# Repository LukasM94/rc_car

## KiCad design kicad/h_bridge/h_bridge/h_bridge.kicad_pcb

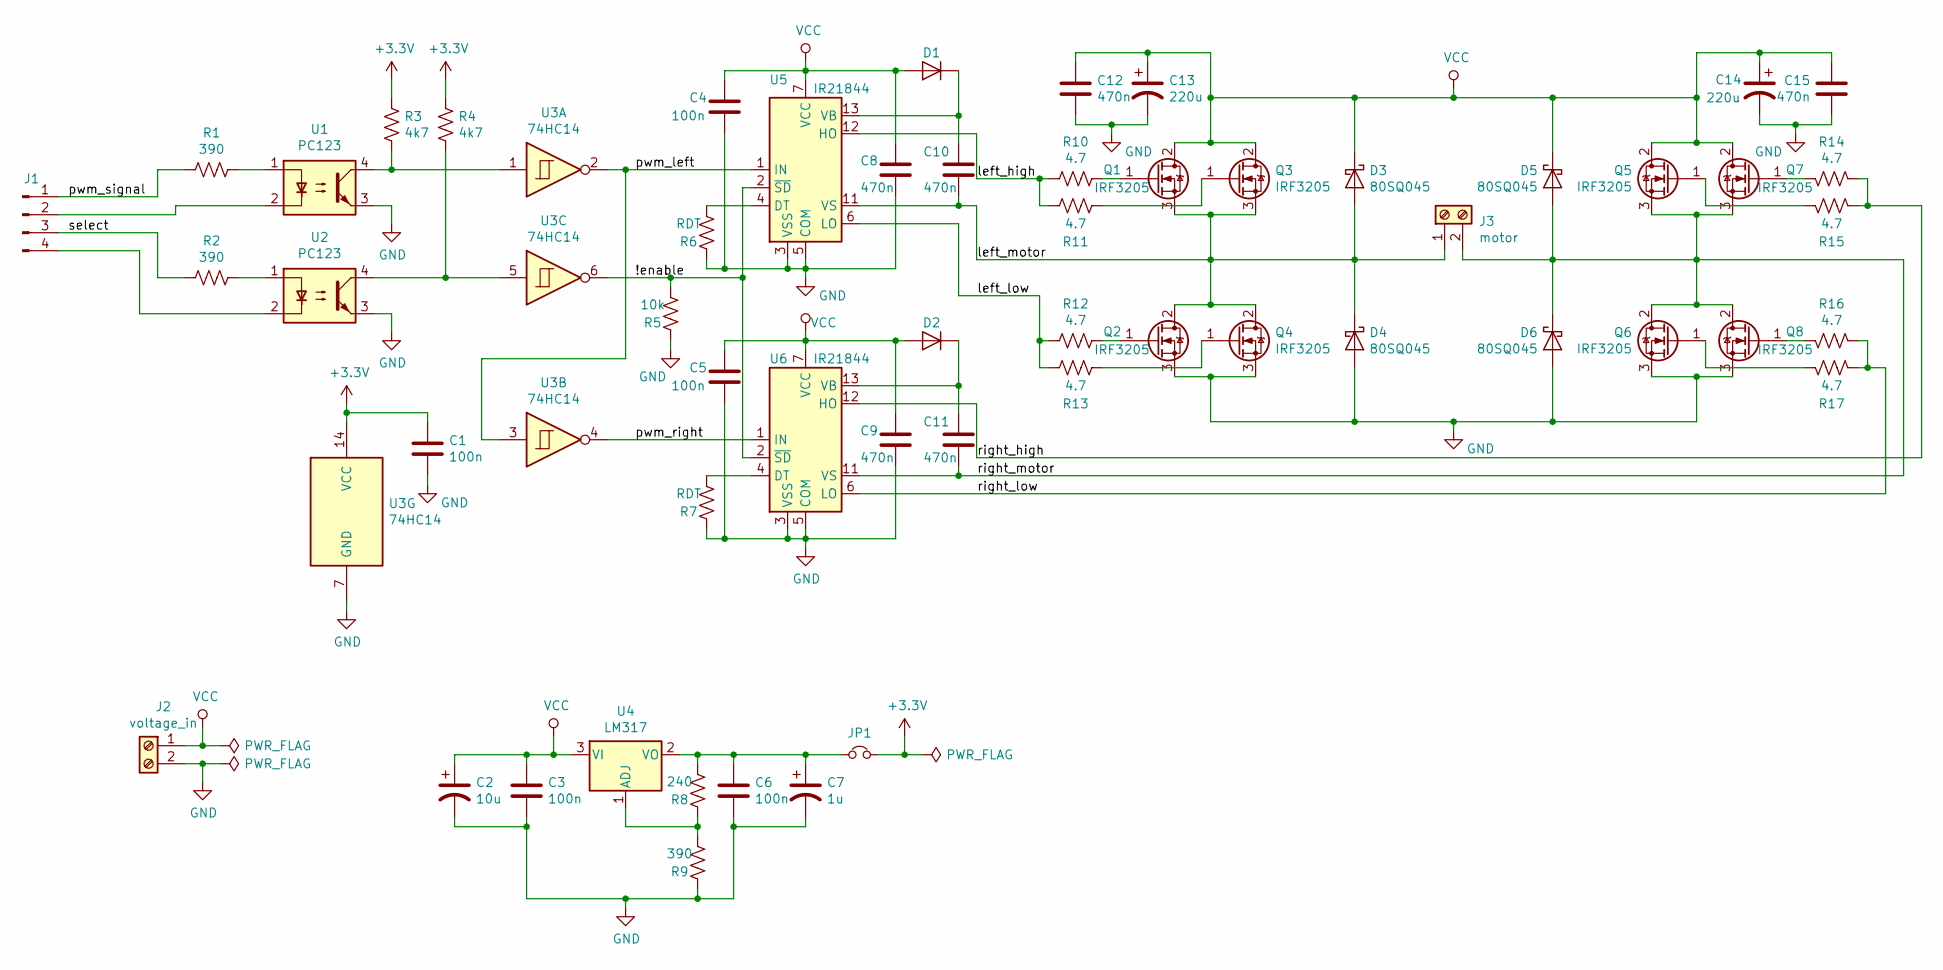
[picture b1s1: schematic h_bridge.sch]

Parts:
C1, C3, C4, C5, C6: 100n; C_0805_2012Metric
C2: 10u; CP_Radial_D5.0mm_P2.50mm
C7: 1u; CP_Radial_D5.0mm_P2.50mm
C8, C9, C10, C11: 470n; C_0805_2012Metric
C12, C15: 470n; C_Rect_L13.0mm_W5.0mm_P10.00mm_FKS3_FKP3_MKS4
C13, C14: 220u; CP_Radial_D10.0mm_P5.00mm
D1, D2: 1N4007; D_DO-41_SOD81_P10.16mm_Horizontal
D3, D4, D5, D6: 80SQ045; D_DO-201AD_P12.70mm_Horizontal
J1: Conn_01x04_Male; PinHeader_1x04_P2.54mm_Vertical
J2: voltage_in; SolderWirePad_1x02_P7.62mm_Drill2.5mm
J3: motor; SolderWirePad_1x02_P7.62mm_Drill2.5mm
JP1: Jumper_NC_Small; PinHeader_1x02_P2.54mm_Vertical
Q1, Q2, Q3, Q4, Q5, Q6, Q7, Q8: IRF3205; TO-220-3_Vertical
R1, R2, R9: 390; R_0805_2012Metric
R3, R4: 4k7; R_0805_2012Metric
R5: 10k; R_0805_2012Metric
R6, R7: RDT; R_0805_2012Metric
R8: 240; R_0805_2012Metric
R10, R11, R12, R13, R14, R15, R16, R17: 4.7; R_0805_2012Metric
U1, U2: PC123; DIP-4_W7.62mm
U3: 74HC14; DIP-14_W7.62mm_LongPads
U4: LM317; TO-220-3_Horizontal_TabDown
U5, U6: IR21844; DIP-14_W7.62mm_LongPads

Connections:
+3V3: C1.1, JP1.2, R3.2, R4.2, U3.14 (VCC)
/!enable: R5.2, U3.6, U5.2 (~SD), U6.2 (~SD)
/left_high: R10.2, R11.2, U5.12 (HO)
/left_low: R12.2, R13.2, U5.6 (LO)
/left_motor: C10.2, D3.2 (A), D4.1 (K), J3.1, Q1.3 (S), Q2.2 (D), Q3.3 (S), Q4.2 (D), U5.11 (VS)
/pwm_left: U3.2, U3.3, U5.1 (IN)
/pwm_right: U3.4, U6.1 (IN)
/pwm_signal: J1.1, R1.2
/right_high: R14.2, R15.2, U6.12 (HO)
/right_low: R16.2, R17.2, U6.6 (LO)
/right_motor: C11.2, D5.2 (A), D6.1 (K), J3.2, Q5.3 (S), Q6.2 (D), Q7.3 (S), Q8.2 (D), U6.11 (VS)
/select: J1.3, R2.2
GND: C1.2, C2.2, C3.2, C4.2, C5.2, C6.2, C7.2, C8.2, C9.2, C12.2, C13.2, C14.2, C15.2, D4.2 (A), D6.2 (A), J2.2, Q2.3 (S), Q4.3 (S), Q6.3 (S), Q8.3 (S), R5.1, R6.1, R7.1, R9.1, U1.3, U2.3, U3.7 (GND), U5.3 (VSS), U5.5 (COM), U6.3 (VSS), U6.5 (COM)
unnamed: C6.1, C7.1, JP1.1, R8.2, U4.2 (VO)
unnamed: C10.1, D1.1 (K), U5.13 (VB)
unnamed: C11.1, D2.1 (K), U6.13 (VB)
unnamed: J1.2, U1.2
unnamed: J1.4, U2.2
unnamed: Q1.1 (G), R10.1
unnamed: Q2.1 (G), R12.1
unnamed: Q3.1 (G), R11.1
unnamed: Q4.1 (G), R13.1
unnamed: Q5.1 (G), R15.1
unnamed: Q6.1 (G), R17.1
unnamed: Q7.1 (G), R14.1
unnamed: Q8.1 (G), R16.1
unnamed: R1.1, U1.1
unnamed: R2.1, U2.1
unnamed: R3.1, U1.4, U3.1
unnamed: R4.1, U2.4, U3.5
unnamed: R6.2, U5.4 (DT)
unnamed: R7.2, U6.4 (DT)
unnamed: R8.1, R9.2, U4.1 (ADJ)
VCC: C2.1, C3.1, C4.1, C5.1, C8.1, C9.1, C12.1, C13.1, C14.1, C15.1, D1.2 (A), D2.2 (A), D3.1 (K), D5.1 (K), J2.1, Q1.2 (D), Q3.2 (D), Q5.2 (D), Q7.2 (D), U4.3 (VI), U5.7 (VCC), U6.7 (VCC)

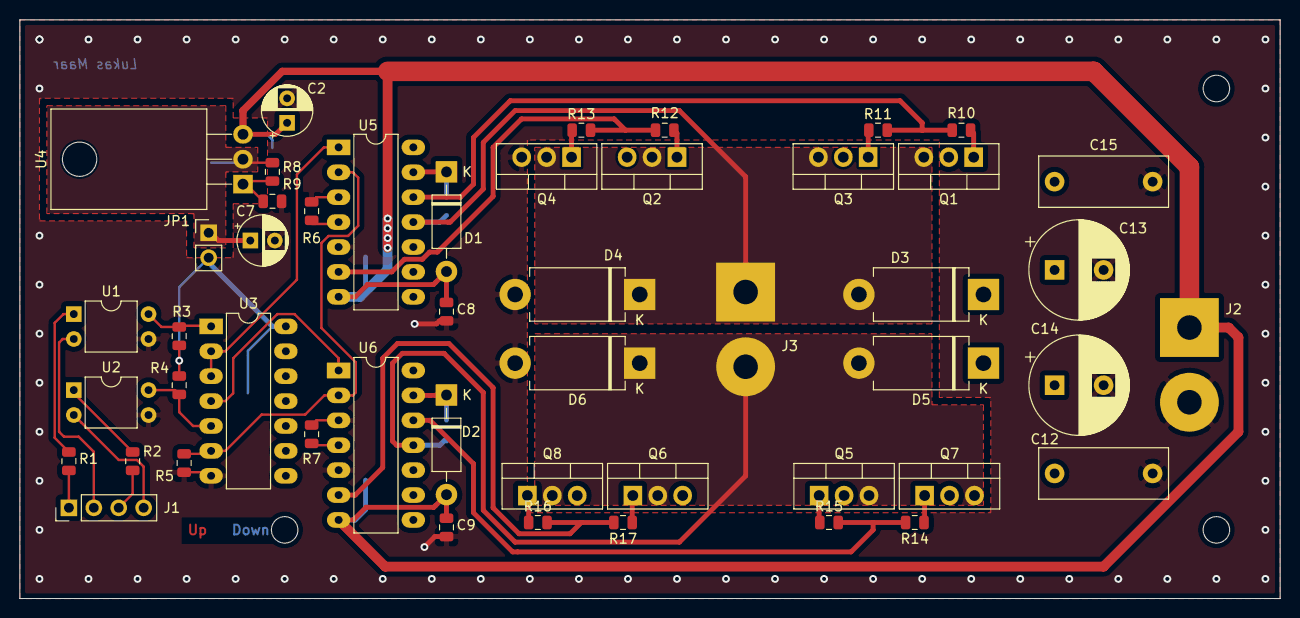
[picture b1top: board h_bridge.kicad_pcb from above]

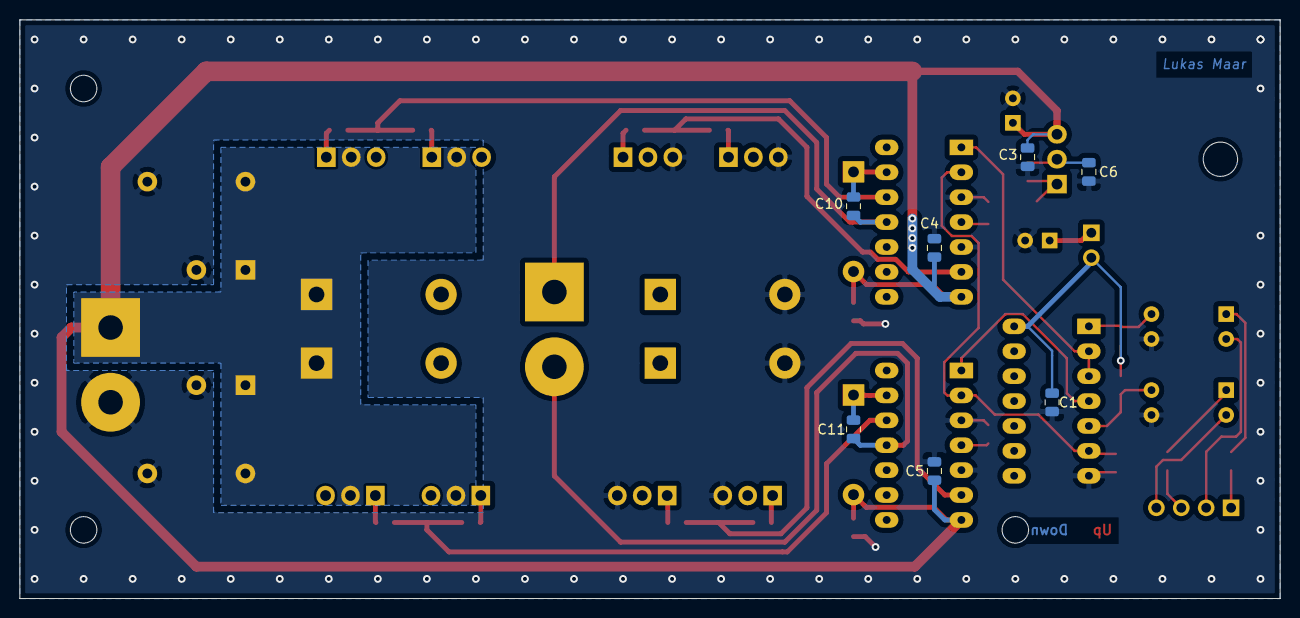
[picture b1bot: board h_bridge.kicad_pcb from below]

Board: 2 copper layers, 128.5 x 59.0 mm, 56 parts (7 on the bottom side), 34 nets.

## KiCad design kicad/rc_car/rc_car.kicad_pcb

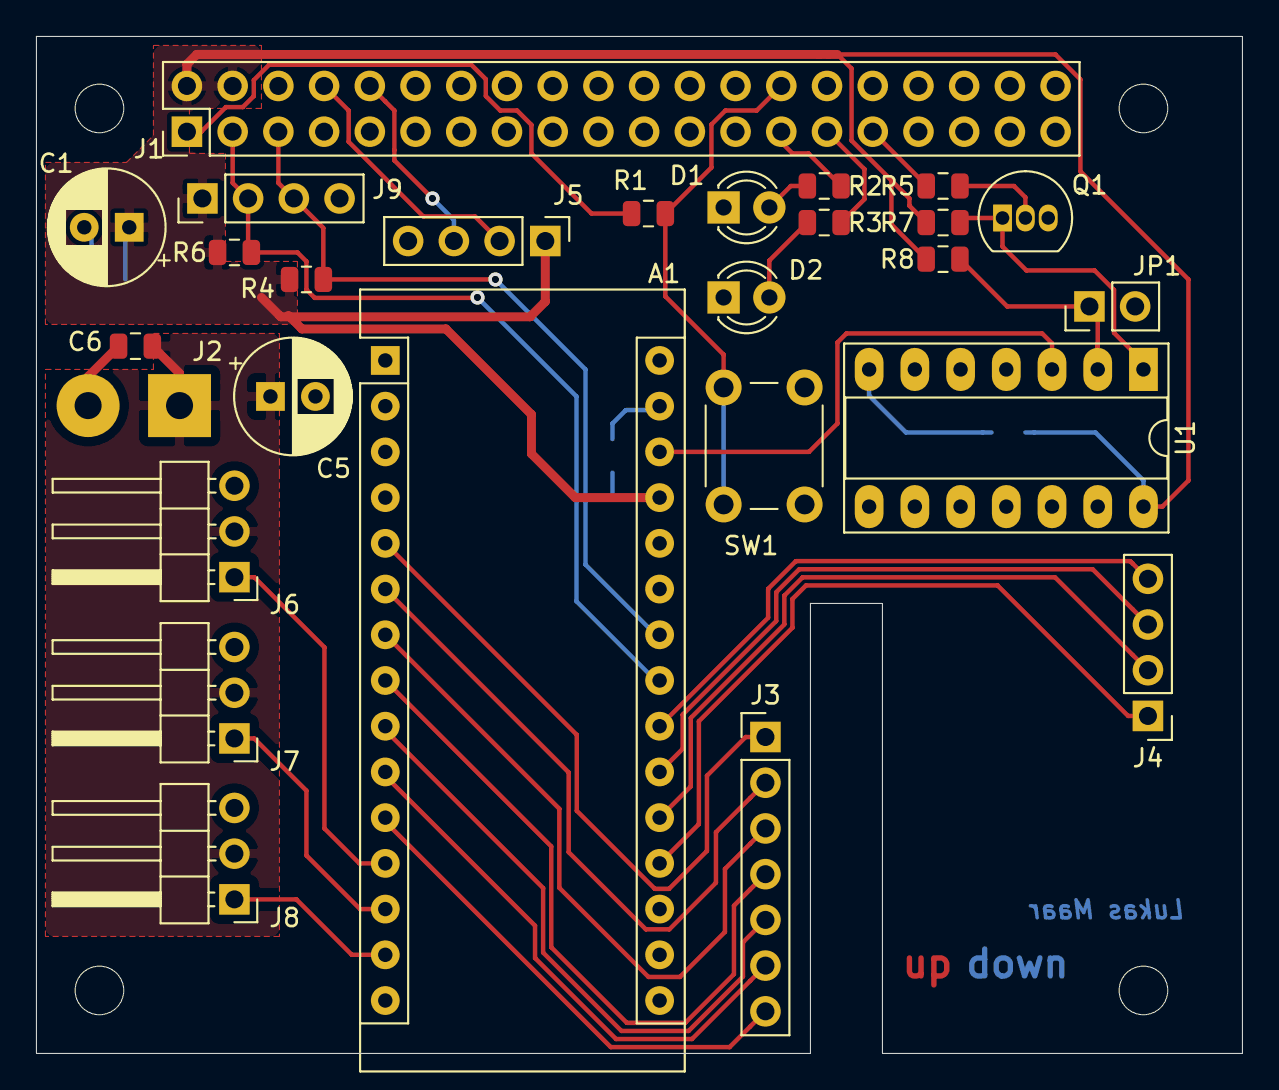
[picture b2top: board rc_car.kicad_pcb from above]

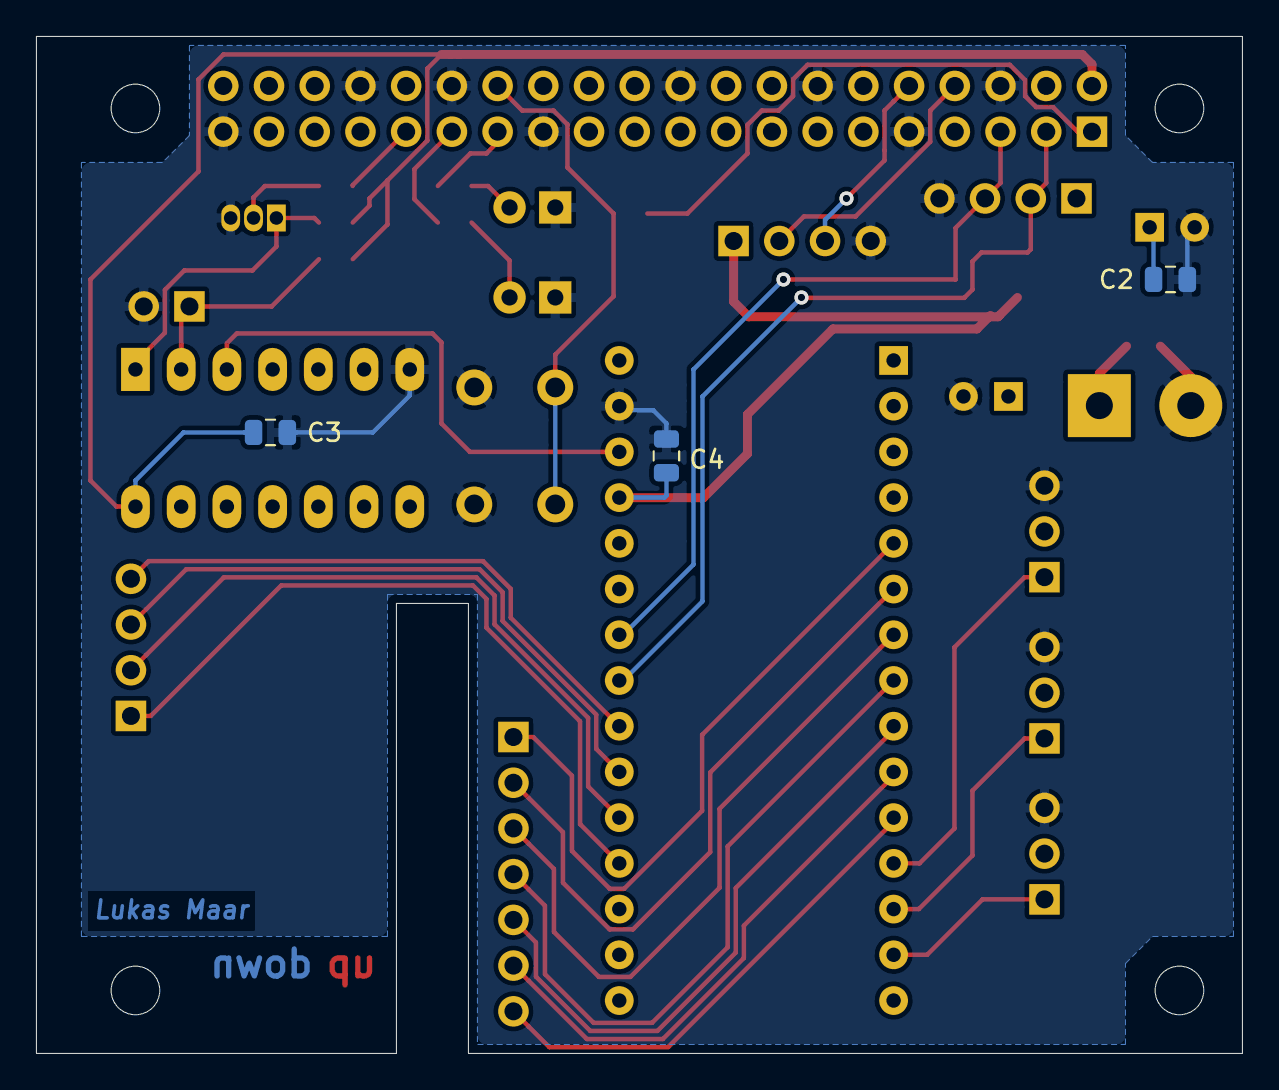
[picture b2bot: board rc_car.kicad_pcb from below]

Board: 2 copper layers, 67.0 x 56.5 mm, 30 parts (3 on the bottom side), 32 nets.

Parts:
A1: Arduino_Nano_v3.x; Arduino_Nano
C1: 10u; CP_Radial_D6.3mm_P2.50mm
C2, C3, C4, C6: 100n; C_0805_2012Metric
C5: 47u; CP_Radial_D6.3mm_P2.50mm
D1, D2: LED; LED_D3.0mm
J1: Raspberry_Pi_2_3; PinHeader_2x20_P2.54mm_Vertical
J2: Screw_Terminal_01x02; SolderWirePad_1x02_P5.08mm_Drill1.5mm
J3: Conn_01x07_Female; PinHeader_1x07_P2.54mm_Vertical
J4, J5: Conn_01x04_Female; PinHeader_1x04_P2.54mm_Vertical
J6, J7, J8: Conn_01x03_Male; PinHeader_1x03_P2.54mm_Horizontal
J9: Conn_01x04_Male; PinHeader_1x04_P2.54mm_Vertical
JP1: Jumper_NO_Small; PinHeader_1x02_P2.54mm_Vertical
Q1: BC547; TO-92_Inline
R1, R7, R8: 10k; R_0805_2012Metric
R2, R3, R5: 1k; R_0805_2012Metric
R4, R6: 2.2k; R_0805_2012Metric
SW1: SW_Push_Dual; SW_PUSH_6mm
U1: 4001; DIP-14_W7.62mm_Socket_LongPads

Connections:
+3V3: J1.1, R1.2
+7.5V: C5.1, C6.1, J2.1, J6.2, J7.2, J8.2
/!reset: A1.28, U1.3
/a0: A1.19, J4.1
/a1: A1.20, J4.2
/a2: A1.21, J4.3
/a3: A1.22, J4.4
/button: J1.28, R1.1, SW1.1
/d2: A1.5, J3.1
/d3: A1.6, J3.2
/d4: A1.7, J3.3
/d5: A1.8, J3.4
/d6: A1.9, J3.5
/d7: A1.10, J3.6
/d8: A1.11, J3.7
/led_green: J1.27, R2.2
/led_red: J1.29, R3.2
/pwm1a: A1.12, J6.1
/pwm1b: A1.13, J7.1
/pwm2: A1.14, J8.1
/rxd: J1.10, J5.3
/scl: A1.24, J1.5, J9.3, R4.2
/sda: A1.23, J1.3, J9.2, R6.2
/txd: J1.8, J5.2
GND: A1.29, C1.2, C2.2, C3.2, C4.2, C5.2, C6.2, D1.1, D2.1, J1.6, J1.9, J1.14, J1.20, J1.25, J1.30, J1.34, J1.39, J2.2, J5.4, J6.3, J7.3, J8.3, J9.4, JP1.2, Q1.3, SW1.2, U1.7
unnamed: D1.2, R2.1
unnamed: D2.2, R3.1
unnamed: J1.31, R5.2
unnamed: JP1.1, R8.2, U1.2
unnamed: Q1.1, R7.2, U1.1
unnamed: Q1.2, R5.1
VCC: A1.27, C1.1, C2.1, C3.1, C4.1, J1.2, J1.4, J5.1, J9.1, R4.1, R6.1, R7.1, R8.1, U1.14

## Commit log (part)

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2020-03-01 [init] copied from ros and restructred
2020-03-01 [control] renamed the main file from control_node to control
2020-03-01 [control] restructured
2020-03-01 [camera] add new project
2020-03-01 [shared] splitted the shared folder in one cpp and one general
2020-03-01 [camera] started playing around
2020-03-01 [camera] simple server client connection
2020-03-02 [cmake; main] changed cmake files; main.cpp is the brain of all; changed the executables to libraries
2020-03-02 [lock] changed to std::lock, because with pthread_lock there was a bug
2020-03-02 [camera] improved python files
2020-03-02 [xbox_controller;camera] python client scripts improved
2020-03-02 [xbox_controller] improved server client connection
2020-03-04 [restructured]
2020-03-05 [renamed] classes start with a big letter
2020-03-05 [control] exchange std::mutex with pthread_mutex
2020-03-05 [control] start with class
2020-03-05 [game_pad_client] seems to work
2020-03-05 [server] added server
2020-03-05 [debug] added
2020-03-05 [config] fixed small bug
2020-03-05 [client][control] improved control
2020-03-05 [debug] improved
2020-03-06 [u_contoller] more abstract now
2020-03-06 [structured]
2020-03-06 [cmake] play around, but did not understand it
2020-03-06 [cmake] changed all libraries to SHARED; now it works with the dependencies
2020-03-06 [gpio] now also a member variable
2020-03-06 [control] now with a tids_ map
2020-03-06 [bug] tried to fix bug
2020-03-06 [bug] try to find the bug
2020-03-06 [bug] neither on linux nor on raspbian works properly
2020-03-06 [bug] fixed
2020-03-06 [game_pad_instance] now there is only one game pad instance; member variables remember how many clients and u controller are active
2020-03-06 [control] now the coordnates of the joystick gets send to the atmega
2020-03-06 [control] fixed a possible race condition
2020-03-06 [server] now restartable threads
2020-03-06 [server] now with atExit
2020-03-06 [server&client] improved loss of connection; the gamepad data gets reset now
2020-03-06 [debug]
2020-03-06 [server] reset gamepad after disconnecting the controller
2020-03-06 [atmega] implemented warning system, after 0.5 sec no i2c signal
2020-03-06 [atmega] added debug possibility
2020-03-07 [pwm] added, but does not work
2020-03-07 [pwm] works now
2020-03-07 [pwm] implemented more beautiful
2020-03-07 [raspberry] own folder; need to change gpio
2020-03-07 [peripherial] added class peripherial and changed the structure
2020-03-08 [atmega&raspberry] connection
2020-03-08 [atmega&raspberry] i2c connection improved; now with offset
2020-03-08 [renamed]
2020-03-08 [config] merged server to shared
2020-03-08 [config]
2020-03-08 [game_pad] better error handling
2020-03-08 [atmega] fixed int8_t bug
2020-03-08 [peripherial] now with red led
2020-03-08 [atmega] gets reset at a new connection
2020-03-08 [game_pad] better exception handling
2020-03-08 [atmega] added eeprom to store offset variables
2020-03-08 [json_exception] forgot to unlock
2020-03-09 [game_pad] try to fix bug
2020-03-09 [game_pad] still a lot of parsing not successful
2020-03-09 [eeprom] now with control register
2020-03-09 [client] added reset pin
2020-03-09 [server] send only strlen of buffer not 1024
2020-03-09 [client&atmega] better hard reset handling
2020-03-09 [client&atmega] reset improved
2020-03-10 [camera] added a class camera
2020-03-10 [server&socket] fixed cmake bug of server and changed socket init to initSocket
2020-03-10 [camera] added basic
2020-03-10 [camera] added init
2020-03-10 [camera] fixed bug
2020-03-12 [camera] can take one single photo
2020-03-12 [camera] now also with lower resolution
2020-03-13 [image] is now an abstract class and only jpeg and rgb are instantiable
2020-03-13 [image] implemented jpeg, but does not work
2020-03-13 [image] jpeg compress and decompress works now
2020-03-13 [image] now in shared folder
2020-03-13 [image] better structured
2020-03-13 [client_handler] added class for handling the client
2020-03-13 [client_handler] splitted client handler
2020-03-13 [shared] moved a lot to shared
2020-03-13 [camera] started with json
2020-03-13 [control] now I have a control instance
2020-03-13 [control] now renamed to control_handler
2020-03-14 [control] renamed it again
2020-03-14 [camera] separated camera and camera_handler
2020-03-14 [camera] implemented a condition variable
2020-03-14 [image] improve json conversion
2020-03-14 [image] another error: premature end of jpeg file
2020-03-14 [image] printed image looks like premature end
2020-03-14 [image] fixed bug
2020-03-14 [camera_client] send now the jpeg image
2020-03-14 [server] adapted to output buffer
2020-03-14 [server_handler] splitted server to server handler and xbox controller service
2020-03-14 [server] restructured
2020-03-14 [client] better error handling
2020-03-14 [server] added camera service
2020-03-14 [server] added thread to camera service
2020-03-14 [server&client] changed struct because of forwarding and started with camera service
2020-03-14 [server&client] common package size
2020-03-14 [package_length] changed to 4096
2020-03-15 [server&client] only packages transmit and receive
2020-03-15 [client] debug
2020-03-15 [server&client] more debug to resolve the bug
2020-03-15 [server&client] now works with package size
2020-03-15 [camera_client] fixed small bug
2020-03-15 [camera] seems to work
2020-03-15 [graphics] now able to display a window with qt
2020-03-15 [graphics] show image basically
2020-03-15 [image_instance] added
2020-03-15 [server] main now more heap
2020-03-15 [graphics] contd
2020-03-15 [client] no join, because of the lock
2020-03-15 [image] print raw
2020-03-15 [client] transmitting warning
2020-03-15 [client] try to find bug
2020-03-15 [server&client] closed socket. fixed bug?
2020-03-15 [server&client] try to find bug
2020-03-15 [server] sig catch
2020-03-15 [client] fixed bug => bug was at laptop. To much established connections
2020-03-15 [server] fixed same bug as client
2020-03-15 [graphics] seems to work
2020-03-15 [graphics] start main window
2020-03-15 [graphics] ui seems to be finished; image does not look good
2020-03-15 [graphics] able to display image
2020-03-15 [graphics] small changes
2020-03-16 [camera] sleep time changed to 40ms
2020-03-16 [shared] structured
2020-03-17 [xbox] wihtout init
2020-03-17 [thread] wrapper now in working thread
2020-03-17 [thread] wrapper now in working thread also on client
2020-03-17 [thread_handler] a static class which handles creation and removing of the threads
2020-03-17 [structure] ctors improved
2020-03-17 [thread_handler] server side done and also improved assert and lock
2020-03-17 [thread_handler] implemented a condition wait
2020-03-17 [thread_handler] started at client
2020-03-17 [server_handler] fixed small memory leak
2020-03-17 [thread_handler] now also at client handler
2020-03-17 [thread_handler] I think every thread uses the thread handler
2020-03-17 [i2c_handler] if there are 5 times in a row no refreshment of the gamepad, i2c_handler will be canceled
2020-03-17 [server_handler] fixed bug
2020-03-17 [camera] deleted python files
2020-03-17 [client] fixed leaked memory
2020-03-18 [server] fixed memroy leak
2020-03-18 [graphics] deleted unnecessary member variables
2020-03-18 [instances] restructured and added a new folder for instances
2020-03-18 [game_pad_instance] implemented to only have one game pad instance
2020-03-18 [game_pad] get data for graphics
2020-03-18 [game_pad&graphics] pretty print at the main window
2020-03-18 [graphics] fixed typo
2020-03-18 [graphics] multithreading with thread handler
2020-03-18 [graphics] the graphic threads are now in the thread handler. the thread handler is able to start external threads. that means those threads are not going to be stored in the list
2020-03-18 [graphics] improved gui
2020-03-18 [graphics] txd and rxd
2020-03-18 [game_pad] transceive now with connected
2020-03-18 [client&atmega] better handling with reset and not connected joystick
2020-03-18 [control] deleted
2020-03-18 [cond] timed wait and better handling in general with sleep
2020-03-18 [client] fixed typo
2020-04-01 [resturcted]
2020-04-01 [control] change structure a little
2020-04-02 [atmega_i2c_handler] added, but not used
2020-04-02 [i2c_handler] implemented atmega i2c handler
2020-04-02 [cond] imroved timed wait
2020-04-02 [raspberry] i2c handler
2020-04-02 [i2c_handler] added i2c writing
2020-04-02 [atmega_i2_handler] added
2020-04-03 [camera] deadlock fixed
2020-04-03 [atmega_i2c_handler] added map for new data
2020-04-03 [i2c] dev address
2020-04-03 [atmega] start changed the main file
2020-04-04 [atmega] i2c works now
2020-04-05 [atmega] structured
2020-04-05 [atmega] implemented abstraction for the i2c registers
2020-04-05 [atmega] save stuff in eeprom
2020-04-05 [pwm] implemented structs for pwm control; have not tested it
2020-04-06 [atmega/i2c_register] implemented a struct which handles all the important stuff
2020-04-06 [atmega/i2c_register] improved struct
2020-04-06 [atmega/pwm] simple writing to pwm works
2020-04-07 [restruct]
2020-04-07 [raspberry/camera] bug fix of the cam. Hardly no overhead if the cam is not connected. One problem: if replug the cam, the raspberry should get restarted
2020-04-07 [atmega/watchdog] added
2020-04-07 [raspberry/camera] only once executed
2020-04-07 [raspberry/camera] improved bug if camera is not plugged in
2020-04-07 [rasperry/atmega_reset] build in on hardware and used the setResetPin function
2020-04-08 [raspberry] better handling with thread list on error situation with the camera
2020-04-08 [raspberry/singleton] more are now singletons
2020-04-08 [raspberry/socket] camera is only running if client handler is connected
2020-04-08 [server/segfault] do not prevent, but should not do any harm to the connection
2020-04-08 [server] added a lot of singletons and the bug (gui stop does not work, if connected broke) is fixed
2020-04-08 [server/ui] added lock
2020-04-08 [server/ui] changed from WorkingThread to QThread
2020-04-08 [kicad/base] schematic done
2020-04-10 [kicad] schematic and layout done
2020-04-10 [kicad/gerber] done
2020-04-10 [kicad/h_bridge] schematic finished
2020-04-10 [kicad/h_bridge] schematic changed ir2184 to ir21844
2020-04-10 [kicad/h_bridge] schematic changed voltage regutlator to lm317
2020-04-11 [kicad/h_bridge] layout improvements; also added gerber
2020-04-11 [kicad/h_bridge] layout done I think
2020-04-11 [kicad/rc_car] wired pins of the atmega to some connectors
2020-04-11 [kicad/h_bridge] gerber file done
2020-04-12 [kicad/h_bridge] small changes
2020-04-12 [gitignore] added gerber.zip
2020-04-13 [kicad/h_bridge] outlines added
2020-04-22 [kicad/h_bridge] gerber
2020-04-22 [atmega/motor_control] renamed
2020-04-22 [rotation_encoder] added
2020-04-22 [attiny] changed to attiny
2020-04-23 [attiny] changed to c++
2020-04-23 [rotation_encoder] changed to c++
2020-04-24 [encoder] contd
2020-04-24 [encoder] now in c again
2020-04-24 [rotation_encoder] direction seems to work; encoder seems to work; timer interrupt seems to work; light barrier seems to work
2020-04-28 [rotation_encoder] changed led pin
2020-05-01 [raspberry&atmega] watchdog 500 ms; raspberry pi sends i2c sync data to atmega; atmega resets itself if no data comes within 500 ms, cause of the watchdog
2020-05-01 [bug] fixed sleep bug of tv_nsec > 1000000000; race condition of cond variable fixed
2020-05-01 [bug] prev bug contd
2020-05-01 [bug] fixed held_by_ bug of Lock
2020-05-02 [atmega] deleted legacy folder
2020-05-02 [atmega/motor_control] communiaction changed
2020-05-02 [atmega] adjusted atmega shell script for the reset pi; fixed sync i2c request
2020-05-03 [cmake] raspberry folder changed to local testing on linux
2020-05-03 [atmega/motor_control] 16 bit now only for servos
2020-05-03 [atmega&debug] adjusted motor_cotrol to the hardware
2020-05-03 [raspberry] less frames, because of latency
2020-05-03 [game_pad] latency added
2020-05-03 [bug] fixed typo
2020-05-03 [raspberry] camera settings
2020-05-04 [raspberry&image] now scale down image possible
2020-05-04 [raspberry] calculate latency and print it on INFO
2020-05-04 [server] implemented latency for gamepad
